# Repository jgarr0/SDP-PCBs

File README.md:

# SDP-PCBs
Hub and Outlet Motherboard Schematics and PCB Layouts for Smart Power Outlet System
#Hub PCB Schematic

## Hub PCB Layout

## Hub PCB Render

## Assembled hub

## Outlet PCB Schematic

## Outlet PCB Layout

## Outlet PCB Render

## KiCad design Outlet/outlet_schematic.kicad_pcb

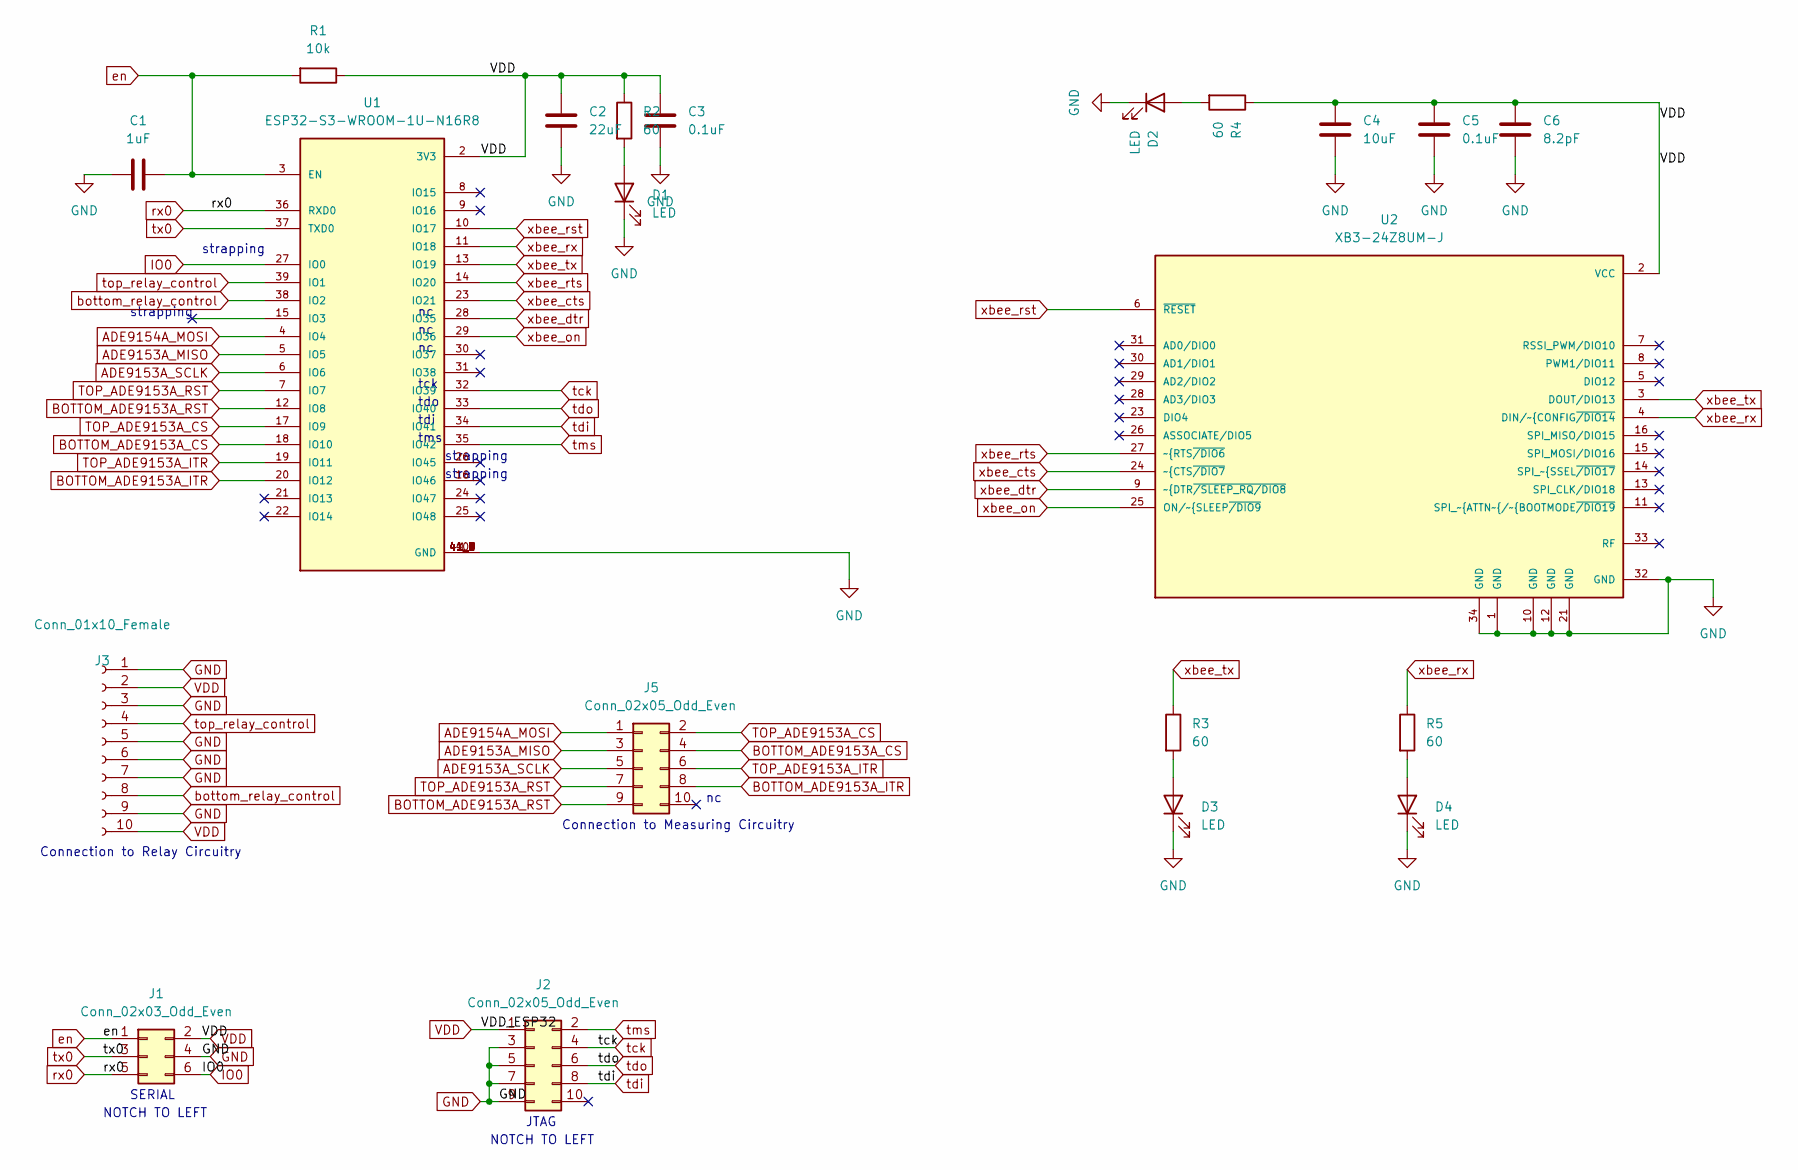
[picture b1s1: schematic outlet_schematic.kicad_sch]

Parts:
C1: 1uF; C_1206_3216Metric
C2: 22uF; C_1206_3216Metric
C3, C5: 0.1uF; C_1206_3216Metric
C4: 10uF; C_1206_3216Metric
C6: 8.2pF; C_1206_3216Metric
D1, D2, D3, D4: LED; LED_1206_3216Metric
J1: Conn_02x03_Odd_Even; IDC-Header_2x03_P2.54mm_Vertical
J2: Conn_02x05_Odd_Even; IDC-Header_2x05_P2.54mm_Vertical
J3: Conn_01x10_Female; JST_PHD_S10B-PHDSS_2x05_P2.00mm_Horizontal
J5: Conn_02x05_Odd_Even; JST_PHD_S10B-PHDSS_2x05_P2.00mm_Horizontal
R1: 10k; R_1206_3216Metric
R2, R3, R4, R5: 60; R_1206_3216Metric
U1: ESP32-S3-WROOM-1U-N16R8; XCVR_ESP32-S3-WROOM-1U; PARTREV v1.1
U2: XB3-24Z8UM-J; XCVR_XB3-24Z8UM-J

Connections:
ADE9153A_MISO: J5.3, U1.5 (IO5)
ADE9153A_SCLK: J5.5, U1.6 (IO6)
ADE9154A_MOSI: J5.1, U1.4 (IO4)
BOTTOM_ADE9153A_CS: J5.4, U1.18 (IO10)
BOTTOM_ADE9153A_ITR: J5.8, U1.20 (IO12)
BOTTOM_ADE9153A_RST: J5.9, U1.12 (IO8)
GND: C1.2, C2.2, C3.2, C4.2, C5.2, C6.2, D1.1 (K), D2.1 (K), D3.1 (K), D4.1 (K), J1.4, J2.3, J2.5, J2.7, J2.9, J3.1, J3.3, J3.5, J3.6, J3.7, J3.9, U1.1 (GND), U1.40 (GND), U1.41_1 (GND), U1.41_2 (GND), U1.41_3 (GND), U1.41_4 (GND), U1.41_5 (GND), U1.41_6 (GND), U1.41_7 (GND), U1.41_8 (GND), U1.41_9 (GND), U2.1 (GND), U2.10 (GND), U2.12 (GND), U2.21 (GND), U2.32 (GND), U2.34 (GND)
IO0: J1.6, U1.27 (IO0)
unnamed: D1.2 (A), R2.2
unnamed: D2.2 (A), R4.2
unnamed: D3.2 (A), R3.2
unnamed: D4.2 (A), R5.2
TOP_ADE9153A_CS: J5.2, U1.17 (IO9)
TOP_ADE9153A_ITR: J5.6, U1.19 (IO11)
TOP_ADE9153A_RST: J5.7, U1.7 (IO7)
VDD: C2.1, C3.1, C4.1, C5.1, C6.1, J1.2, J2.1, J3.2, J3.10, R1.1, R2.1, R4.1, U1.2 (3V3), U2.2 (VCC)
bottom_relay_control: J3.8, U1.38 (IO2)
en: C1.1, J1.1, R1.2, U1.3 (EN)
rx0: J1.5, U1.36 (RXD0)
tck: J2.4, U1.32 (IO39)
tdi: J2.8, U1.34 (IO41)
tdo: J2.6, U1.33 (IO40)
tms: J2.2, U1.35 (IO42)
top_relay_control: J3.4, U1.39 (IO1)
tx0: J1.3, U1.37 (TXD0)
xbee_cts: U1.23 (IO21), U2.24 (~CTS~{/DIO7)
xbee_dtr: U1.28 (IO35), U2.9 (~DTR~{/SLEEP_RQ/DIO8)
xbee_on: U1.29 (IO36), U2.25 (ON/~SLEEP~{/DIO9)
xbee_rst: U1.10 (IO17), U2.6 (~RESET)
xbee_rts: U1.14 (IO20), U2.27 (~RTS~{/DIO6)
xbee_rx: R5.1, U1.11 (IO18), U2.4 (DIN/~CONFIG~{/DIO14)
xbee_tx: R3.1, U1.13 (IO19), U2.3 (DOUT/DIO13)

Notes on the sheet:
tms
strapping
Connection to Relay Circuitry
tdi
JTAG
NOTCH TO LEFT
tck
tdo
Connection to Measuring Circuitry
SERIAL

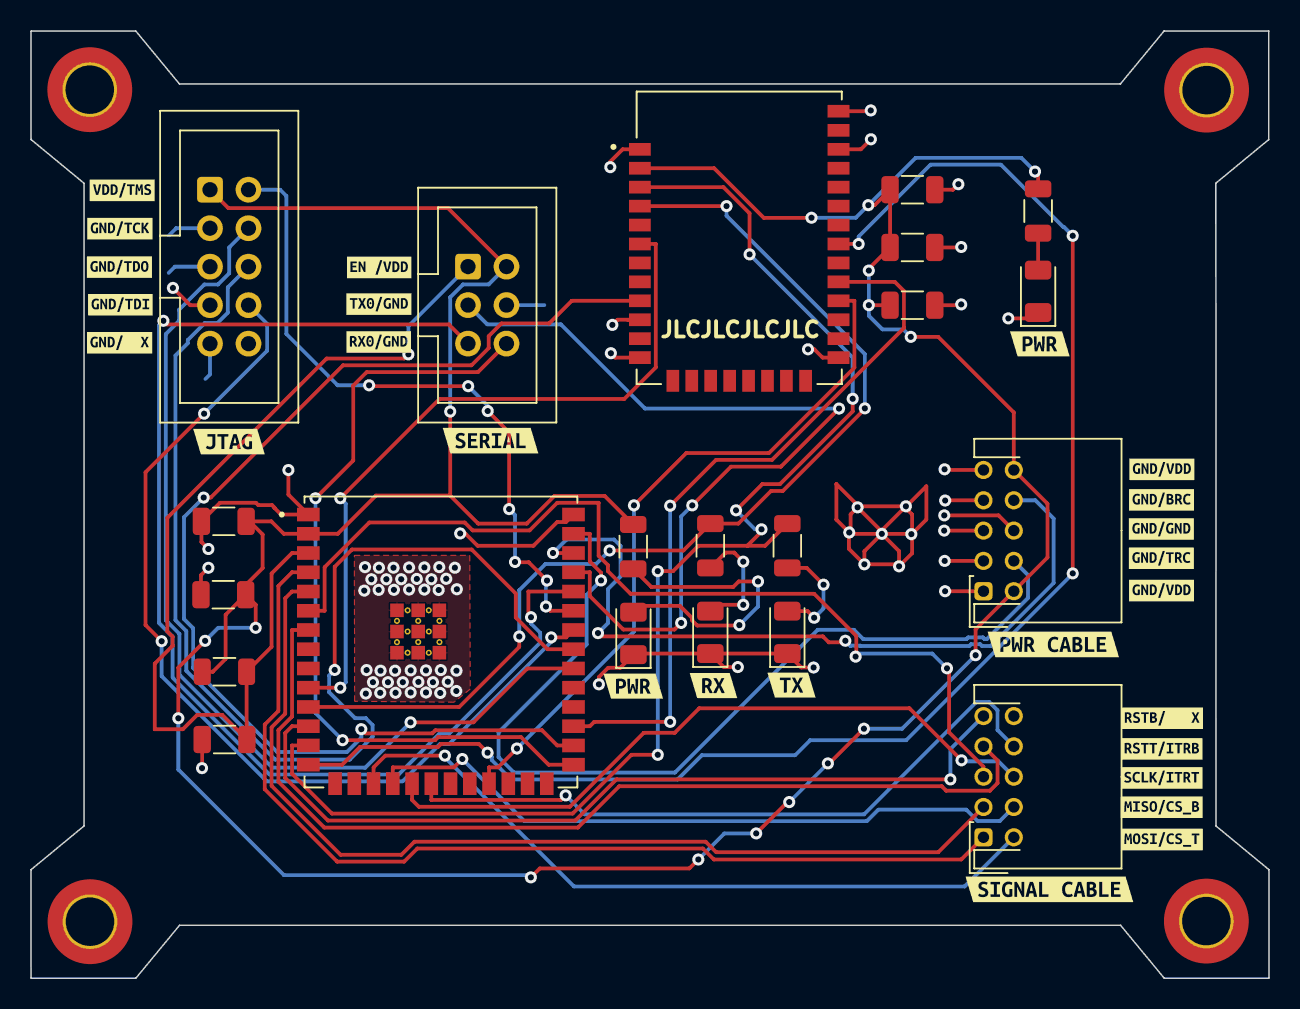
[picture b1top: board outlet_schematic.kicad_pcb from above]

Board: 2 copper layers, 81.7 x 62.5 mm, 51 parts (0 on the bottom side), 32 nets.

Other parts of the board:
MP1, MP2, MP3, MP4: MountingHole_3.2mm_M3_DIN965_Pad_TopBottom
kibuzzard-6423A409: G***; kibuzzard-6423A409
kibuzzard-64222CB8, kibuzzard-64222CB8#2: G***; kibuzzard-64222CB8
kibuzzard-64222D10: G***; kibuzzard-64222D10
kibuzzard-64222D21: G***; kibuzzard-64222D21
kibuzzard-64222DA8: G***; kibuzzard-64222DA8
kibuzzard-64222DBC: G***; kibuzzard-64222DBC
kibuzzard-64222E4F: G***; kibuzzard-64222E4F
kibuzzard-64222ED4: G***; kibuzzard-64222ED4
kibuzzard-64222F0B: G***; kibuzzard-64222F0B
kibuzzard-64222F2D: G***; kibuzzard-64222F2D
kibuzzard-64222F16: G***; kibuzzard-64222F16
kibuzzard-6422303A: G***; kibuzzard-6422303A
kibuzzard-6422317A: G***; kibuzzard-6422317A
kibuzzard-6422318F: G***; kibuzzard-6422318F
kibuzzard-6422332A: G***; kibuzzard-6422332A
kibuzzard-6422333F: G***; kibuzzard-6422333F
kibuzzard-64223004: G***; kibuzzard-64223004
kibuzzard-64223022: G***; kibuzzard-64223022
kibuzzard-64223074: G***; kibuzzard-64223074
kibuzzard-64223167: G***; kibuzzard-64223167
kibuzzard-64223170: G***; kibuzzard-64223170
kibuzzard-64223187: G***; kibuzzard-64223187
kibuzzard-64223322: G***; kibuzzard-64223322
kibuzzard-64223346: G***; kibuzzard-64223346
kibuzzard-64223357: G***; kibuzzard-64223357

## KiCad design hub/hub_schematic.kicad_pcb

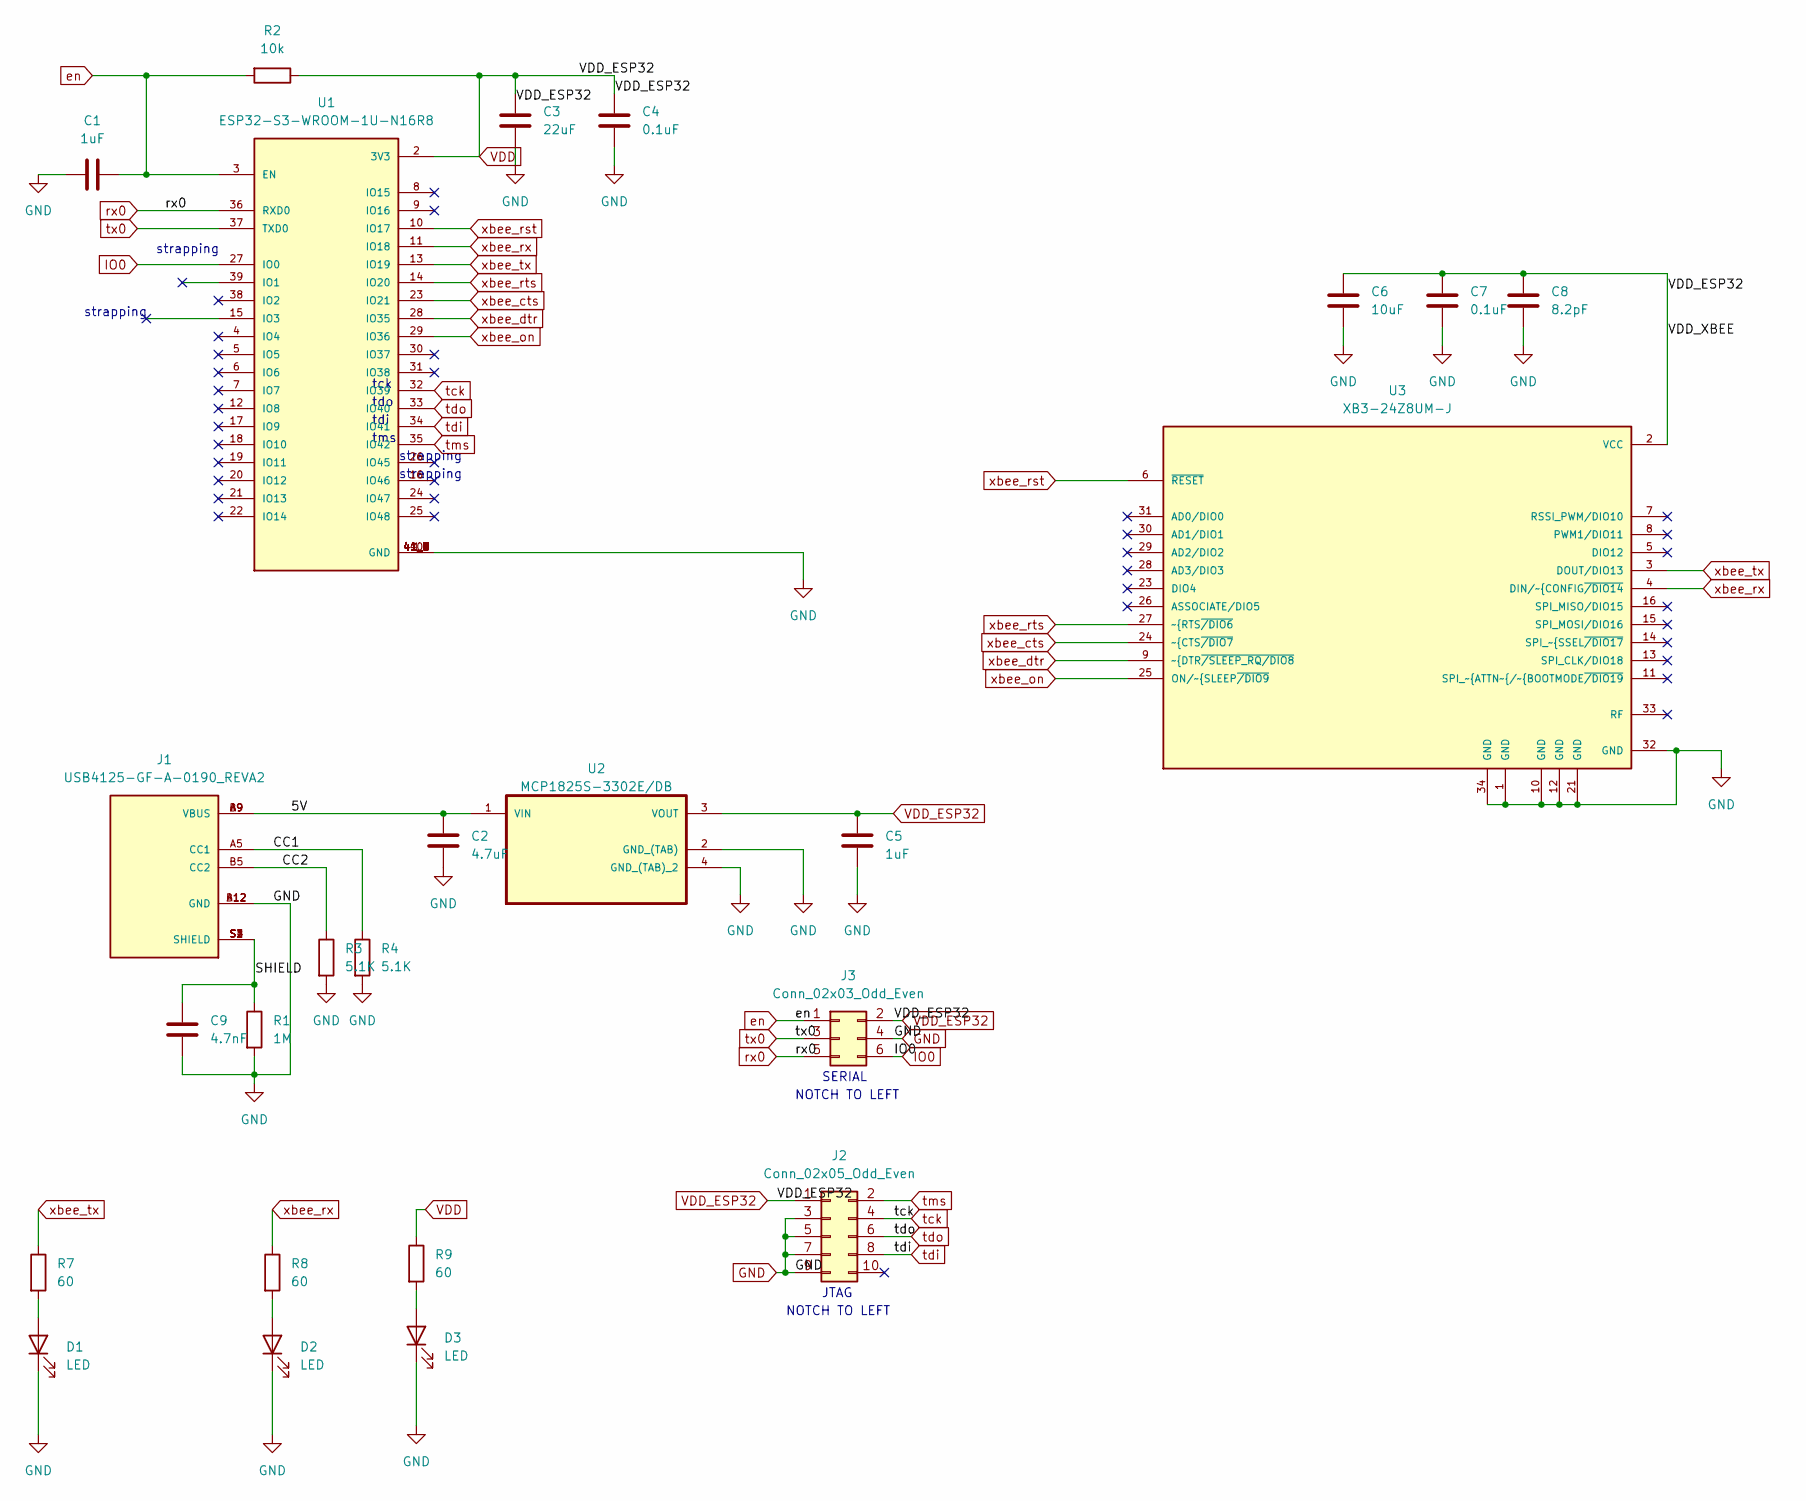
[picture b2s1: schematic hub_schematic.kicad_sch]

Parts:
C1, C5: 1uF; C_1206_3216Metric_Pad1.33x1.80mm_HandSolder
C2: 4.7uF; C_1206_3216Metric_Pad1.33x1.80mm_HandSolder
C3: 22uF; C_1206_3216Metric_Pad1.33x1.80mm_HandSolder
C4, C7: 0.1uF; C_1206_3216Metric_Pad1.33x1.80mm_HandSolder
C6: 10uF; C_1206_3216Metric_Pad1.33x1.80mm_HandSolder
C8: 8.2pF; C_1206_3216Metric_Pad1.33x1.80mm_HandSolder
C9: 4.7nF; C_1206_3216Metric_Pad1.33x1.80mm_HandSolder
D1, D2, D3: LED; LED_1206_3216Metric_Pad1.42x1.75mm_HandSolder
J1: USB4125-GF-A-0190_REVA2; GCT_USB4125-GF-A-0190_REVA2; PARTREV Rev A2
J2: Conn_02x05_Odd_Even; IDC-Header_2x05_P2.54mm_Vertical
J3: Conn_02x03_Odd_Even; IDC-Header_2x03_P2.54mm_Vertical
R1: 1M; R_1206_3216Metric_Pad1.30x1.75mm_HandSolder
R2: 10k; R_1206_3216Metric_Pad1.30x1.75mm_HandSolder
R3, R4: 5.1K; R_1206_3216Metric_Pad1.30x1.75mm_HandSolder
R7, R8, R9: 60; R_1206_3216Metric_Pad1.30x1.75mm_HandSolder
U1: ESP32-S3-WROOM-1U-N16R8; XCVR_ESP32-S3-WROOM-1U; PARTREV v1.1
U2: MCP1825S-3302E/DB; SOT230P700X180-4N
U3: XB3-24Z8UM-J; XCVR_XB3-24Z8UM-J

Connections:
/5V: C2.1, J1.A9 (VBUS), J1.B9 (VBUS), U2.1 (VIN)
/CC1: J1.A5 (CC1), R4.1
/CC2: J1.B5 (CC2), R3.1
/SHIELD: C9.1, J1.S1 (SHIELD), J1.S2 (SHIELD), J1.S3 (SHIELD), J1.S4 (SHIELD), R1.1
GND: C1.2, C2.2, C3.2, C4.2, C5.2, C6.2, C7.2, C8.2, C9.2, D1.1 (K), D2.1 (K), D3.1 (K), J1.A12 (GND), J1.B12 (GND), J2.3, J2.5, J2.7, J2.9, J3.4, R1.2, R3.2, R4.2, U1.1 (GND), U1.40 (GND), U1.41_1 (GND), U1.41_2 (GND), U1.41_3 (GND), U1.41_4 (GND), U1.41_5 (GND), U1.41_6 (GND), U1.41_7 (GND), U1.41_8 (GND), U1.41_9 (GND), U2.2 (GND_(TAB)), U2.4 (GND_(TAB)_2), U3.1 (GND), U3.10 (GND), U3.12 (GND), U3.21 (GND), U3.32 (GND), U3.34 (GND)
IO0: J3.6, U1.27 (IO0)
unnamed: D1.2 (A), R7.2
unnamed: D2.2 (A), R8.2
unnamed: D3.2 (A), R9.2
VDD: C3.1, C4.1, C5.1, C6.1, C7.1, C8.1, J2.1, J3.2, R2.1, R9.1, U1.2 (3V3), U2.3 (VOUT), U3.2 (VCC)
en: C1.1, J3.1, R2.2, U1.3 (EN)
rx0: J3.5, U1.36 (RXD0)
tck: J2.4, U1.32 (IO39)
tdi: J2.8, U1.34 (IO41)
tdo: J2.6, U1.33 (IO40)
tms: J2.2, U1.35 (IO42)
tx0: J3.3, U1.37 (TXD0)
xbee_cts: U1.23 (IO21), U3.24 (~CTS~{/DIO7)
xbee_dtr: U1.28 (IO35), U3.9 (~DTR~{/SLEEP_RQ/DIO8)
xbee_on: U1.29 (IO36), U3.25 (ON/~SLEEP~{/DIO9)
xbee_rst: U1.10 (IO17), U3.6 (~RESET)
xbee_rts: U1.14 (IO20), U3.27 (~RTS~{/DIO6)
xbee_rx: R8.1, U1.11 (IO18), U3.4 (DIN/~CONFIG~{/DIO14)
xbee_tx: R7.1, U1.13 (IO19), U3.3 (DOUT/DIO13)

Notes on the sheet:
tms
strapping
tdi
JTAG
NOTCH TO LEFT
tck
tdo
SERIAL

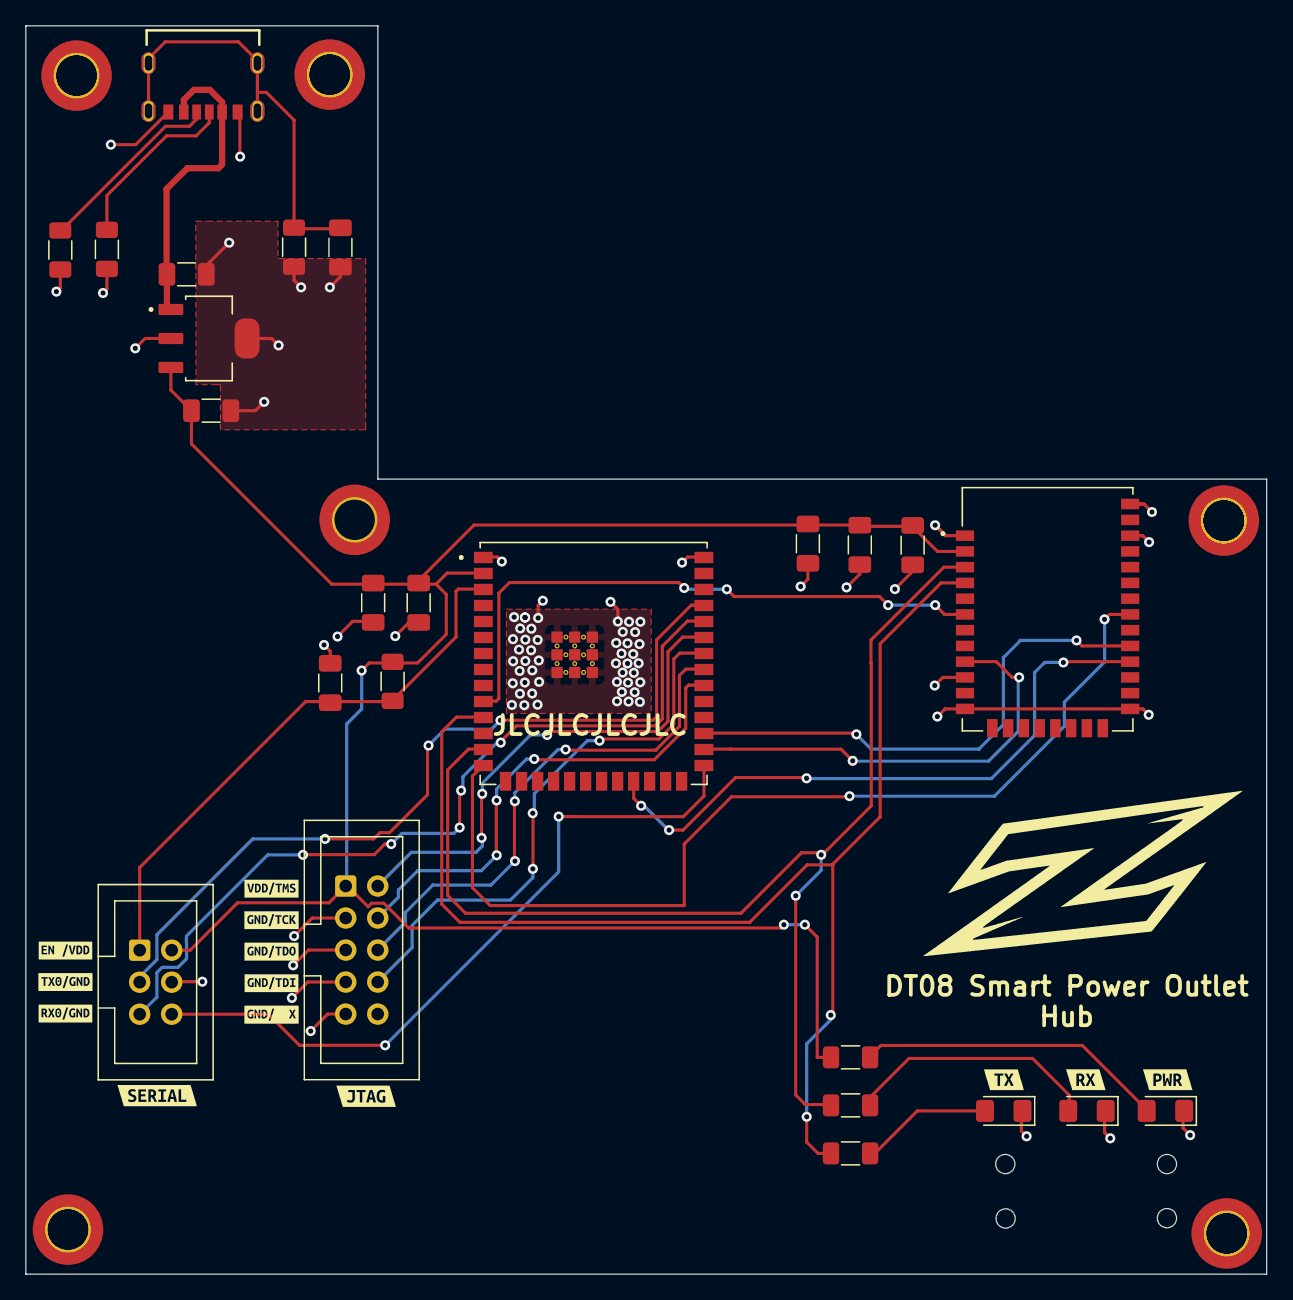
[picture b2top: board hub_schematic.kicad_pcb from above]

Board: 2 copper layers, 98.5 x 99.1 mm, 38 parts (0 on the bottom side), 24 nets.

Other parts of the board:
kibuzzard-6423A4A2: G***; kibuzzard-6423A4A2
kibuzzard-6423A4AE: G***; kibuzzard-6423A4AE
kibuzzard-6423A4B6: G***; kibuzzard-6423A4B6
kibuzzard-6423A4BC: G***; kibuzzard-6423A4BC
kibuzzard-6423A4C5: G***; kibuzzard-6423A4C5
kibuzzard-6423A5A2: G***; kibuzzard-6423A5A2
kibuzzard-6423A5A6: G***; kibuzzard-6423A5A6
kibuzzard-6423A5AD: G***; kibuzzard-6423A5AD
kibuzzard-6423A409: G***; kibuzzard-6423A409
kibuzzard-6423A486: G***; kibuzzard-6423A486
kibuzzard-6422303A: G***; kibuzzard-6422303A
kibuzzard-64223004: G***; kibuzzard-64223004
kibuzzard-64223022: G***; kibuzzard-64223022

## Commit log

2023-04-03 Upload Final PCBs
